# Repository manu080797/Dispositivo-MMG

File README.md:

# Mecanomiografía: desarrollo de un dispositivo para el monitoreo del límite de fatiga muscular

## Descripción del repositorio

Este es el repositorio del proyecto integrador "Mecanomiografía: desarrollo de un dispositivo para el monitoreo del límite de fatiga muscular" para la carrera de ingeniería mecánica en el <a href="https://www.ib.edu.ar">Instituto Balseiro</a>. En la carpeta <a href="https://github.com/manu080797/Dispositivo-MMG/tree/main/Documentos">Documentos</a> se incluye una <a href="https://github.com/manu080797/Dispositivo-MMG/raw/main/Documentos/Presentación%20final.pptx.zip">presentación de PowerPoint</a> que sirve como introducción al trabajo realizado. Además, se incluye la <a href="https://github.com/manu080797/Dispositivo-MMG/raw/main/Documentos/Mecanomiograf%C3%ADa%20desarrollo%20de%20un%20dispositivo%20para%20el%20monitoreo%20del%20l%C3%ADmite%20de%20fatiga%20muscular.pdf">tesis completa</a> en formato PDF. En la carpeta <a href="https://github.com/manu080797/Dispositivo-MMG/tree/main/Programas">Programas</a> se encuentra el código de los tres programas desarrollados durante el proyecto.  En la carpeta <a href="https://github.com/manu080797/Dispositivo-MMG/tree/main/Electrónica">Electrónica</a> están los archivos de <a href="https://www.kicad.org">KiCAD</a> utilizados para diseñar y construir los circuitos electrónicos del dispositivo. Por último, en la carpeta <a href="https://github.com/manu080797/Dispositivo-MMG/tree/main/Carcasa">Carcasa</a> se incluyen archivos de <a href="https://solidedge.siemens.com/en/solutions/products/complete-product-development-portfolio/whats-new-in-solid-edge-2021/">SolidEdge 2021</a> con el modelo 3D de la carcasa del dispositivo, la cual fue construida con una impresora 3D.

## Resumen
En esta tesis se desarrolló un dispositivo de adquisición de señal para mecanomiografía de bajo costo, replicable y portátil. El mismo consta de un acelerómetro, electrónica de acondicionamiento de señal y una placa de desarrollo en la que se adquieren las señales de dos canales en simultáneo. Estas se procesan digitalmente y son transmitidas de manera inalámbrica a una aplicación multiplataforma de control y comunicación también desarrollada en este trabajo. Esta aplicación permite visualizar las señales en tiempo real y almacenar capturas. Estas se procesan fuera de línea según una metodología también diseñada en este trabajo para determinar qué parámetros de la señal se relacionan con la actividad muscular. Los parámetros se calcularon sobre la señal original, sobre bandas de frecuencia específicas y sobre la distribución espectral de potencia. Por último, se realizaron experimentos para aplicar la metodología propuesta a las señales adquiridas por el dispositivo desarrollado. Se realizaron ejercicios isométricos de extensión de rodilla sobre un brazo de reacción fijo vinculado a una celda de carga. Se midió la señal de mecanomiografía sobre el recto femoral de 5 sujetos en ejercicios a carga máxima, a distintos porcentajes de la carga máxima, y hasta el fallo de la tarea solicitada; y se realizaron pruebas de impacto sobre el músculo para evaluar las propiedades mecánicas del mismo. Se procesaron 145 parámetros, de los cuales se encontraron 12 con alta correlación con la fuerza ejercida (coeficiente de correlación r de Pearson ≥ 0,8). Con las pruebas de impacto se encontró que la frecuencia natural del músculo aumenta con la fuerza. En ejercicios al fallo de la tarea solicitada, se encontró que los 12 parámetros seleccionados mantienen el valor esperado con la correlación hallada, para la carga del ejercicio, durante al menos 10 segundos, y luego presentan desviaciones significativas, pero con sentidos variados entre sujetos. Los parámetros relacionados con la energía de la señal en la banda de 50 a 75 Hz presentaron una correlación superior al resto (r = 0,9) y desviaciones con el tiempo en los ejercicios al fallo consistentes en todos los sujetos y cargas evaluadas.

### Descripción del dispositivo

### Arquitectura del dispositivo

### Arreglo experimental

### Señal cruda en ejercicio al fallo de la tarea solicitada

### Procesamiento de señal

### 1) Señal cruda 2) Subbanda de frecuencia 3) Parámetro

## Abstract
A low cost, replicable and portable signal acquisition device for mechanomiography was developed in this thesis. It comprises an accelerometer, its signal conditioning electronics and a development board that acquires the signal in two channels. The signal is digitally processed and wirelessly transmitted to a multi-platform control and communication App, which is also developed in this thesis. This App enables the realtime visualization of the signal and its storage for offline processing, using a methodology designed in this thesis to get correlated features with muscle activity. These features where computed over the original signal, some band filtered components and the power spectrum density. Finally, experiments where conducted to apply the developed methodology to the signal acquired by the device. These experiments consisted of isometric knee extension exercises against a fixed reaction arm linked to a load cell. The mechanomiogram signal was acquired from the rectus femoris muscle of 5 participants at maximum load, at intermediate loads, and to task failure. Additionally, bump tests where conducted to evaluate the muscle mechanical properties. 145 features where processed, of which only 12 showed a high correlation with force (Pearson’s r correlation coefficient ≥ 0,8). Muscle natural frequency was found to increase with higher force production. The 12 selected parameters presented a constant value during the first 10 seconds of a fatiguing exercise, but showed significant deviations from the expected value after this, with varying directions between subjects. From the selected features, those related with the signal energy at the 50-75 Hz band presented both the highest correlation (r = 0,9) and the most consistent deviations sense, in task failure exercises among all subjects and loads.

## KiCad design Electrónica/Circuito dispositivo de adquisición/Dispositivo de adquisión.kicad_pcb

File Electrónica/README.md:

# Electrónica

Diagramas esquemáticos y PCB de los circuitos desarrollados. Los mismos se desarrollaron utilizando el software KiCad v5.0.1.

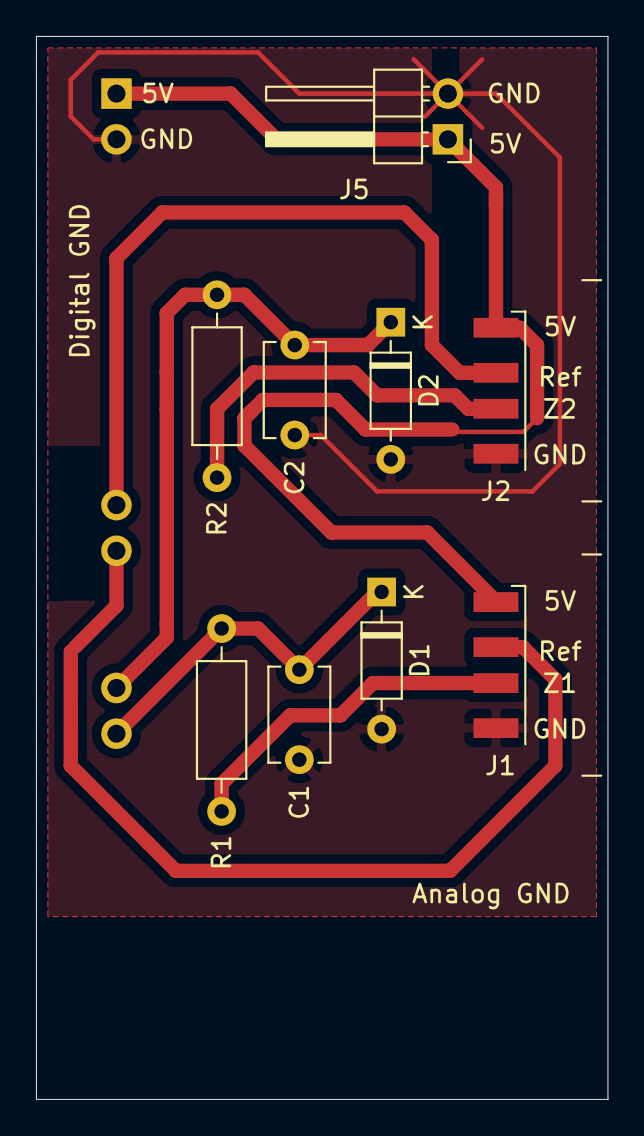
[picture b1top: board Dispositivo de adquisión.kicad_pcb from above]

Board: 2 copper layers, 31.7 x 59.1 mm, 10 parts (1 on the bottom side), 8 nets.

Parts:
C1, C2: 330n; C_Disc_D5.1mm_W3.2mm_P5.00mm
D1, D2: BAT43; D_DO-35_SOD27_P7.62mm_Horizontal
J1, J2: USB_A; USB_A_CNCTech_1001-011-01101_Horizontal
J3: Conn_01x18; PinHeader_1x18_P2.54mm_Vertical
J5: Conn_01x02; PinHeader_1x02_P2.54mm_Horizontal
R1, R2: 2.2k; R_Axial_DIN0207_L6.3mm_D2.5mm_P10.16mm_Horizontal

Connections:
+5V: J1.1, J2.1, J3.1, J5.1
GND: C1.2, C2.2, D1.2, D2.2, J1.4, J2.4, J3.2, J5.2
unnamed: C1.1, D1.1, J3.15, R1.2
unnamed: C2.1, D2.1, J3.14, R2.2
unnamed: J1.2, J3.11
unnamed: J1.3, R1.1
unnamed: J2.2, J3.10
unnamed: J2.3, R2.1

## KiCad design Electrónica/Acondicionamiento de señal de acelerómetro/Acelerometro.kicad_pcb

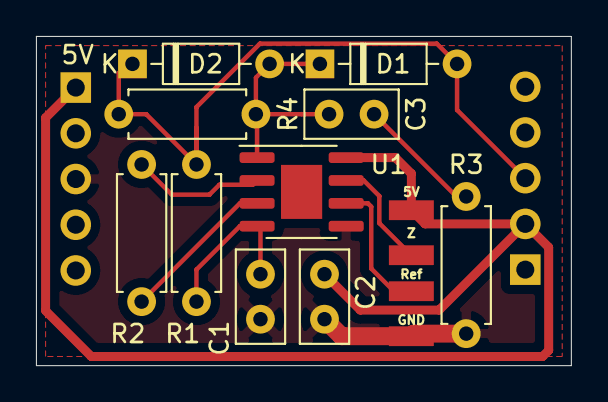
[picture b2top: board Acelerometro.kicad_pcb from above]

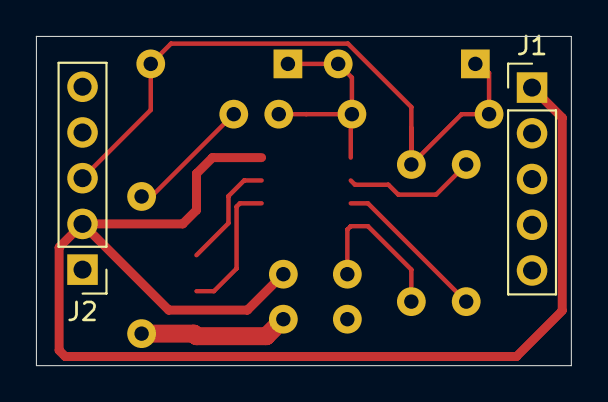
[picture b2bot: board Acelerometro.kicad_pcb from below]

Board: 2 copper layers, 29.7 x 18.3 mm, 13 parts (2 on the bottom side), 10 nets.

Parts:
C1: 470p; C_Disc_D5.0mm_W2.5mm_P2.50mm
C2: 100n; C_Disc_D5.0mm_W2.5mm_P2.50mm
C3: 470n; C_Disc_D5.0mm_W2.5mm_P2.50mm
D1, D2: D_Schottky; D_DO-35_SOD27_P7.62mm_Horizontal
J1, J2: Conn_01x05_Male; PinHeader_1x05_P2.54mm_Vertical
R1, R4: 220k; R_Axial_DIN0207_L6.3mm_D2.5mm_P7.62mm_Horizontal
R2, R3: 5.6k; R_Axial_DIN0207_L6.3mm_D2.5mm_P7.62mm_Horizontal
U1: AD8226; SOIC-8-1EP_3.9x4.9mm_P1.27mm_EP2.29x3mm
USB_Cable_Connector1: Conn_01x04; USB_A_CNCTech_1001-011-01101_Horizontal

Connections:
GND: C1.2, C2.2, J1.3, R3.2, U1.5, USB_Cable_Connector1.4
unnamed: C1.1, R1.2, U1.4
unnamed: C2.1, J1.1, J2.2, U1.8, USB_Cable_Connector1.1
unnamed: C3.1, D1.1, D2.2, R4.2, U1.1
unnamed: C3.2, R3.1
unnamed: D1.2, D2.1, J2.3, R1.1, R4.1
unnamed: R2.1, U1.3
unnamed: R2.2, U1.2
unnamed: U1.6, USB_Cable_Connector1.3
unnamed: U1.7, USB_Cable_Connector1.2

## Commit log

2021-08-10 Initial release
2021-08-10 Include thesis PDF
2021-08-13 Versión final tesis
2021-09-06 Versión final - entrega biblioteca
